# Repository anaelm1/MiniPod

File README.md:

# MiniPod 

MiniPod is a simple MP3 player which functions using the Arduino Nano, and even has an OLED Display. It has an Audio Jack for the output and plays songs from a MicroSD card. 

It is made so that I can listen to songs offline and without the distractions of a Smartphone in environments like the GYM. It is inspired by the Apple Ipod.

## Features:
- 3D printed body with 6 buttons for controls. 
- 128x32 OLED Display to display current song and artists.
- 6 controls (Pause/Play, Previous, Next, Vol up, Vol down).
- Usb C charging port

## CAD Model:
The pcb is attached to the base at a height of 5mm using 4 M3 screws to have enough space for the battery. The top plate is attached to the body using smaller M1 screws and heat inserts due to narrow walls. 

It has 8 separate printed pieces. The base where the PCB sits, the top cover, the 6 hand made buttons, and the side power button. The project and my name is embossed on the top plate as well.

Made in Fusion360. 

## PCB
Here's my PCB! It was made in KiCad. The components are placed on both sides of the PCB to save space.

Schematic

PCB

## Firmware Overview
MiniPod uses two programs for firmware. 

-A python script which renames all songs into simple indexes (000-999), so that they can be easily accesed by the DFPlayer Mini. It also creates a csv file linking all indexes to their song names.

-The main Ardunio script written in C which runs the MiniPod and all its functions. (I used C, because I learned it a few months ago while doing Harvards CS50x).

- The buttons will be hand labelled. 
- There is Vol up and Vol down option as well. 
- The OLED is the song name, artist name, index, and playing status.

## AI Usage:
While I tried to keep AI usage minimum, it was used for these things: 

-All the research and finalization of the components.

-Fusion360 controls help

-Major help in the Ardunio part of the firmware. I tried to not copy paste any code at all, at least not without understanding it first. 

## MicroSD Card Format

Your MicroSD card must be formatted to **FAT16/FAT32** and contain an `index.csv` file in the root folder using the following format:

csv

Index,Title,Artist

000,Bohemian Rhapsody,Queen

001,Hotel California,Eagles

002,Billie Jean,Michael Jackson

## BOM:
These are the components used in the GamePad 9:

-Arduino Nano

-DFPlayer Mini MP3 Audio Player Module

-TRRS Module PJ-320A 3.5mm Female Audio Jack Connector

-0.96 inch I2C SSD1306 128x64 OLED Display Module

-3.7V LiPo Battery 

-TP4056 + Boost Charger Module

-SPDT Power Switch

-5 Tactile Switch 6x6

-1k Ohm Resistor

-2 2.54mm Single Row Female Pin Header Strip

-2 2.54mm Single Row Male Pin Header Strip

-M1.6 Heat-Set Brass Inserts

-M1.6 Machine Screws

-M3 Screws

-3D printed body

## Info
This is my first solo hardware project. Please let me know if you spot any kind a flaw!

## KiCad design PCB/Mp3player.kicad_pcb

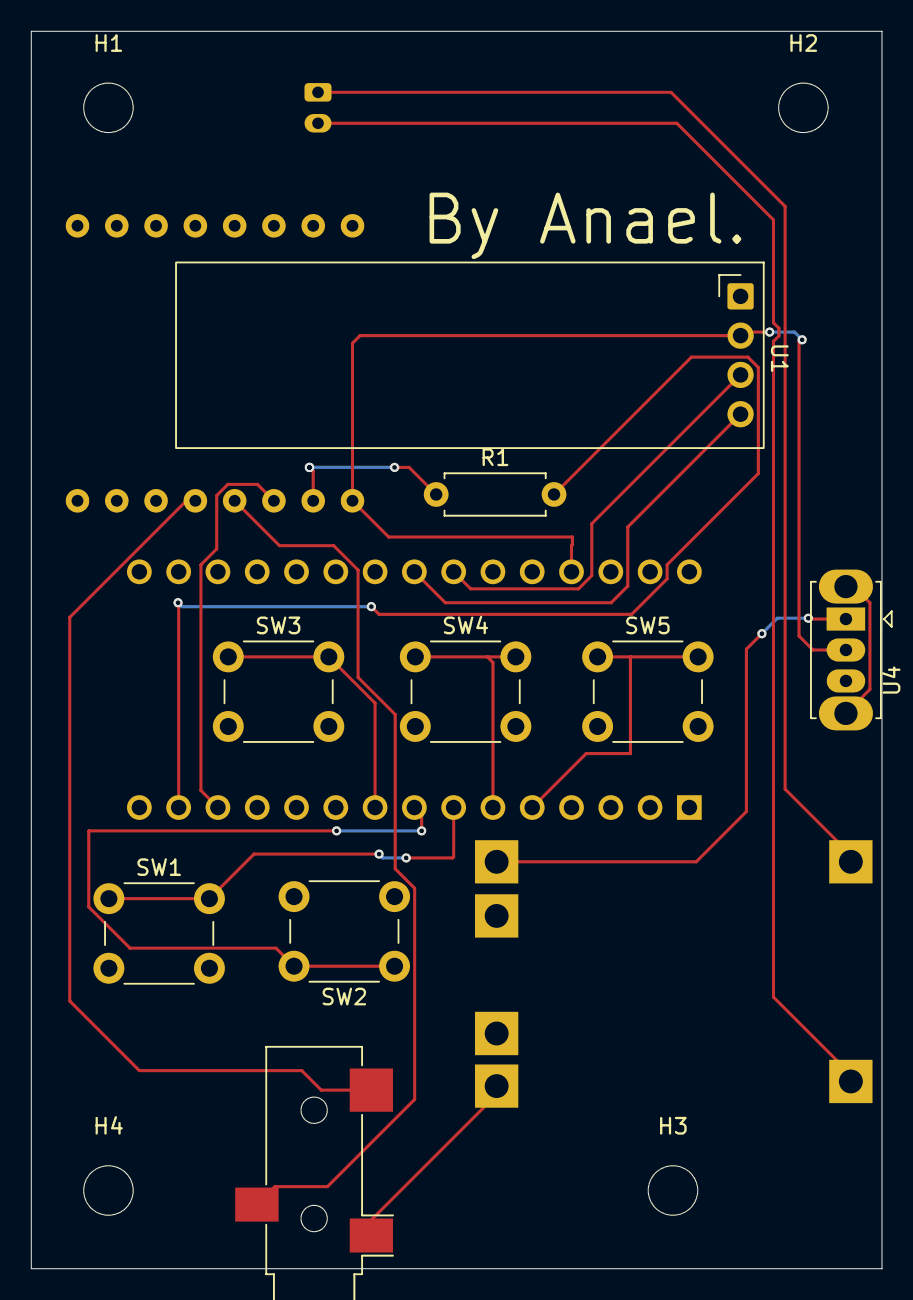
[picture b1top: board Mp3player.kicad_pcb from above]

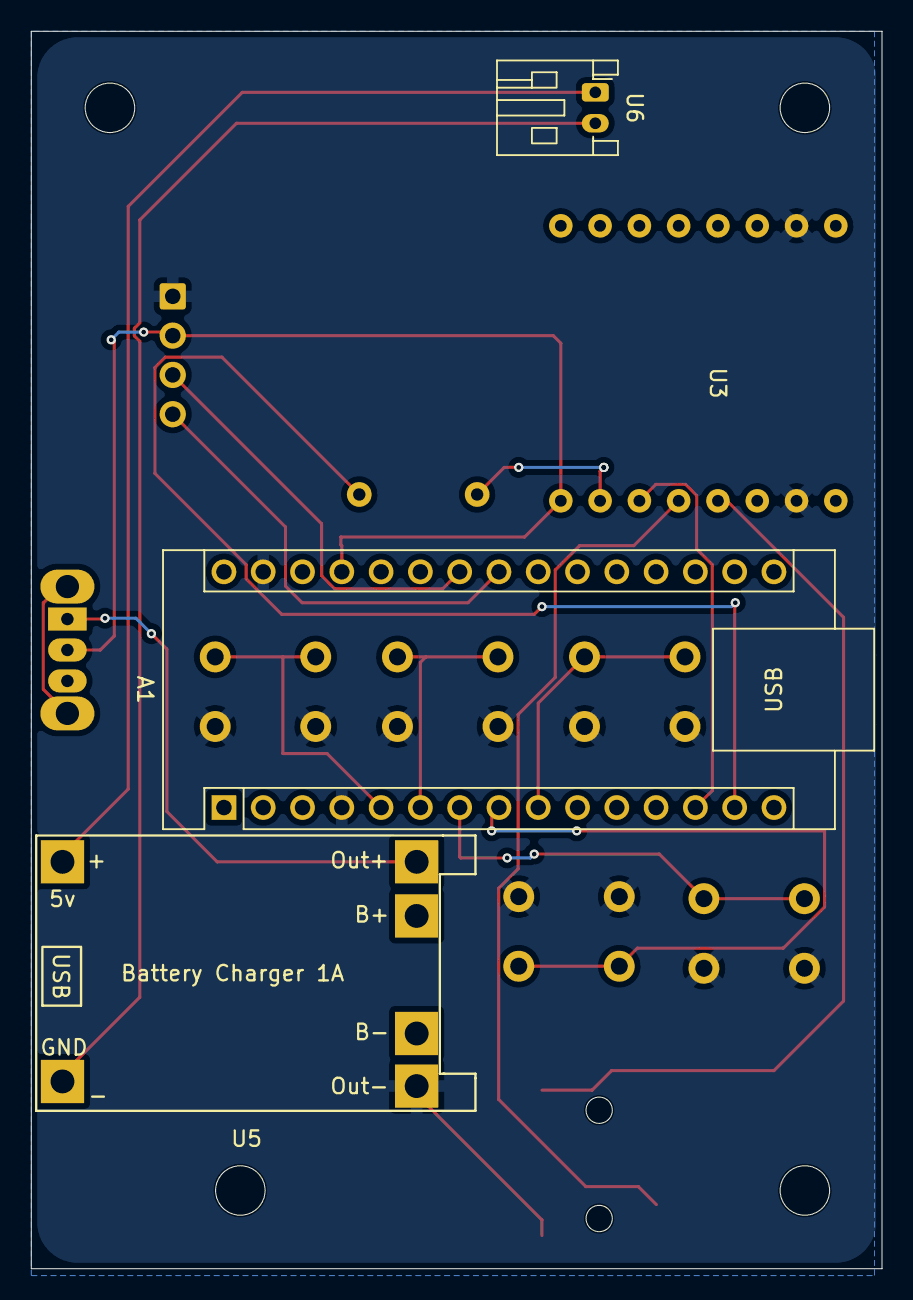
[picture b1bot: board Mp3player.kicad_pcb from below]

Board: 2 copper layers, 55.0 x 80.0 mm, 17 parts (4 on the bottom side), 17 nets.

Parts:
A1: Arduino_Nano
H1, H2, H3, H4: MountingHole; MountingHole_3.2mm_M3
R1: 1k; R_Axial_DIN0207_L6.3mm_D2.5mm_P7.62mm_Horizontal
SW1, SW2, SW3, SW4, SW5: SW_Push; SW_PUSH_6mm_H5mm
U1: ER_OLEDM0.91_1x-I2C
U3: DFPlayer
U4: SW_Slide_SPDT_Straight_CK_OS102011MS2Q
U5: TP4056-18650
U6: JST_PH_S2B-PH-K_1x02_P2.00mm_Horizontal
U7: Jack_3.5mm_CUI_SJ-3523-SMT_Horizontal

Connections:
5V: A1.27 (VUSB/5V), U1.2 (VCC), U3.1 (VCC), U4.2 (OUT)
GND: A1.4 (GND), A1.29 (GND), SW1.2, SW2.2, SW3.2, SW4.2, SW5.2, U1.1 (GND), U3.7 (GND), U3.10 (GND), U5.4 (OUT-), U7.S (GND)
unnamed: A1.5 (D2), SW5.1
unnamed: A1.6 (D3), SW4.1
unnamed: A1.7 (D4), SW1.1
unnamed: A1.8 (D5), SW2.1
unnamed: A1.9 (D6), SW3.1
unnamed: A1.13 (D10/CS), U3.3 (TX)
unnamed: A1.14 (D11/COPI), R1.2
unnamed: U3.5 (DAC_L), U7.T (DAC_L)
unnamed: U3.4 (DAC_R), U7.R (DAC_R)
unnamed: R1.1, U3.2 (RX)
unnamed: U4.1 (IN), U5.3 (OUT+)
unnamed: U5.1 (BAT+), U6.1 (BAT+)
unnamed: U5.2 (BAT-), U6.2 (BAT-)
SCL: A1.24 (SCL/A5), U1.3 (SCL)
SDA: A1.23 (SDA/A4), U1.4 (SDA)
